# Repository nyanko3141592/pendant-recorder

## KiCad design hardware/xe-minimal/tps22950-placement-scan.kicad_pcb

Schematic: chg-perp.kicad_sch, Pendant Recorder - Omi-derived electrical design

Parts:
C1, C2, C3, C6, C9, C22, C26: 100n; C_0402_1005Metric
C4: 10u; C_0603_1608Metric
C5: 4.7u; C_0603_1608Metric
C7, C16, C25: 1u; C_0402_1005Metric
C13: 2.2u 10V; C_0402_1005Metric
C14: 2.2u; C_0402_1005Metric
C15: 10u 10V effective >=1u; C_0603_1608Metric
C27: 4.7u effective TBD; C_0603_1608Metric
C28: 10n; C_0402_1005Metric
C29: 100n 10V; C_0402_1005Metric
C30: 50p 50V C0G; C_0402_1005Metric
D6: TJ-S1005SW4TGLC9Y-A5 amber LED; LED_0402_1005Metric
J1: USB4105-GF-A (candidate); USB_C_GCT_USB4105_GroundLand112
J2: Molex781710003 / DTP401525-XE; Molex_Pico-EZmate_78171-0003_1x03-1MP_P1.20mm_Vertical
J3: Factory SWD pogo candidate; SWD_Pogo_5Pad_P1.27mm
Q3, Q4: DMN63D8L-7; SOT-23
R1: 0R; R_0402_1005Metric
R2: 10k; R_0402_1005Metric
R3, R4, R13, R15, R22: 100k; R_0402_1005Metric
R6, R7: 5.1k 1%; R_0402_1005Metric
R10: 6.8k 1%; R_0402_1005Metric
R11, R39: 20k 1%; R_0402_1005Metric
R12, R36, R37, R38, R40: 100k 1%; R_0402_1005Metric
R14: 1M; R_0402_1005Metric
R21, R23: 22R tentative; R_0402_1005Metric
R24, R25, R28: 47k; R_0402_1005Metric
R32: 6.8k tentative; R_0402_1005Metric
R33, R34: 1M 1%; R_0402_1005Metric
R35: 10k 1%; R_0402_1005Metric
R41: 7.5k 1%; R_0402_1005Metric
R42: PTFR0402B24K0P9 24k 0.1%; R_0402_1005Metric
R43: 4.7k 1%; R_0402_1005Metric
R51: 0R 1%; R_0402_1005Metric
SW1: B3U-1000P (candidate); SW_SPST_B3U-1000P
TH1: NCU18XH103F60RB 10k 1% B3380; R_0603_1608Metric
TP1, TP2, TP3, TP5, TP6: TestPoint; TestPoint_Pad_D1.0mm
U1: STM32U585CIU6; QFN-48-1EP_7x7mm_P0.5mm_EP5.6x5.6mm
U2: USBLC6-2P6; SOT-666
U3: BQ25185DLHR; Texas_DLH0010A_WSON-10-1EP_2.2x2mm_P0.4mm_EP0.9x1.5mm
U4: TPS7A0233PDBVR; SOT-23-5
U8: IM69D130V01; IM69D130_JLC_SMD_trial
U10: TPS22917DBVT; SOT-23-6
U11: CSNP32GCR01-BOW candidate; CSNP32GCR01_LGA8
U12: TLV7042DDFR; SOT-23-8

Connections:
/BAT: C14.1, J2.1 (PACK_PLUS), R33.1, TP1.1, U3.2 (BAT)
/BAT_ADC: C28.1, R33.2, R34.1, U1.11 (PA1)
/BAT_TS: J2.2 (PACK_NTC_10K), R37.2, TH1.1 (SENSE), U12.2 (INA-), U12.5 (INB+)
/BOOT0: R3.1, U1.44 (PH3)
/BUTTON_N: R4.2, SW1.1, U1.38 (PA15)
/CC1: J1.A5 (CC1), R6.1
/CC2: J1.B5 (CC2), R7.1
/CHARGER_TS: R35.1, U3.6 (TS_MR)
/CHG_ALLOW: R43.1, U1.20 (PB2)
/CHG_GUARD_GATE: Q4.1 (G), R36.1, R43.2, U12.1 (OUTA), U12.7 (OUTB)
/CHG_INHIBIT_GATE: Q4.3 (D), R12.2, U3.4 (CE_N)
/CHG_N: R11.2, U1.27 (PB14), U3.9 (STAT1)
/ILIM_VSET: R42.1, U3.7 (ILIM_VSET)
/ISET: C30.1, R10.1, U3.8 (ISET)
/NRST: C9.1, J3.3 (nRESET), R2.2, U1.7 (NRST)
/PDM_CLK: R21.2, U8.3 (CLOCK)
/PDM_CLK_MCU: R21.1, U1.39 (PB3)
/PDM_DATA: U1.40 (PB4), U8.1 (DATA)
/SD_CLK: R23.2, U11.3 (CLK)
/SD_CLK_MCU: R23.1, U1.15 (PA5)
/SD_CS_N: R28.2, U1.14 (PA4), U11.2 (CS_N)
/SD_EN: R22.1, U1.41 (PB5), U10.2 (ON)
/SD_MISO: R25.2, U1.16 (PA6), U11.6 (DO)
/SD_MOSI: R24.2, U1.17 (PA7), U11.5 (DI)
/SD_V3: C26.1, C27.1, R24.1, R25.1, R28.1, TP5.1, U10.5 (QOD), U10.6 (VOUT), U11.8 (VDD)
/STATUS_LED: R32.1, U1.29 (PA8)
/STATUS_LED_A: D6.2 (A), R32.2
/SWCLK: J3.4 (SWCLK), U1.37 (PA14)
/SWDIO: J3.2 (SWDIO), U1.34 (PA13)
/TS_COLD_REF: R38.2, R39.1, U12.3 (INA+)
/TS_HOT_REF: R40.2, R41.1, U12.6 (INB-)
/USB_DM: J1.A7 (D-), J1.B7 (D-), U1.32 (PA11), U2.3 (IO2), U2.4 (IO2)
/USB_DP: J1.A6 (D+), J1.B6 (D+), U1.33 (PA12), U2.1 (IO1), U2.6 (IO1)
/V3V3: C1.1, C2.1, C3.1, C4.1, C16.1, C22.1, C25.1, C29.1, J3.1 (VTref), R1.1, R2.1, R4.1, R11.1, R15.1, R37.1, R38.1, R40.1, TP3.1, U1.1 (VBAT), U1.24 (VDD), U1.36 (VDD), U1.48 (VDD), U4.5 (OUT), U8.2 (VDD), U10.1 (VIN), U12.8 (VCC)
/VBUS_GATE: Q3.1 (G), R13.2, R14.1
/VBUS_N: Q3.3 (D), R15.2, U1.10 (PA0)
/VCAP: C5.1, U1.22 (VCAP)
/VDDA: C6.1, C7.1, R1.2, U1.9 (VDDA)

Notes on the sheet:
01 MCU / RTC / UI
02 USB-C / CHARGER
03 POWER / FUEL GAUGE
04 AUDIO / SD / INDICATORS
ENGINEERING DRAFT - NOT FOR FABRICATION - See hardware/xe-minimal/README.md

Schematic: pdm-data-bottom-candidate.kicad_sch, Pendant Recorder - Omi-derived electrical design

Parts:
C1, C2, C3, C6, C9, C22, C26: 100n; C_0402_1005Metric
C4: 10u; C_0603_1608Metric
C5, C27: 4.7u; C_0603_1608Metric
C7, C16, C25: 1u; C_0402_1005Metric
C13: 2.2u 10V; C_0402_1005Metric
C14: 2.2u; C_0402_1005Metric
C15: 10u 10V effective >=1u; C_0603_1608Metric
C28: 10n; C_0402_1005Metric
C29: 100n 10V; C_0402_1005Metric
C30: 50p 50V C0G; C_0402_1005Metric
D6: TJ-S1005SW4TGLC9Y-A5 amber LED; LED_0402_1005Metric
J1: USB4105-GF-A; USB_C_GCT_USB4105_GroundLand112
J2: Molex781710003 / DTP401525-XE; Molex_Pico-EZmate_78171-0003_1x03-1MP_P1.20mm_Vertical
J3: Factory SWD pogo pads; SWD_Pogo_5Pad_P1.27mm
Q3, Q4: DMN63D8L-7; SOT-23
R1: 0R; R_0402_1005Metric
R2: 10k; R_0402_1005Metric
R3, R4, R13, R15, R22: 100k; R_0402_1005Metric
R6, R7: 5.1k 1%; R_0402_1005Metric
R10: RC0402FR-0730KL 30k 1%; R_0402_1005Metric
R11, R39: 20k 1%; R_0402_1005Metric
R12, R36, R37, R38, R40: 100k 1%; R_0402_1005Metric
R14: 1M; R_0402_1005Metric
R21, R23: 22R tentative; R_0402_1005Metric
R24, R25, R28: 47k; R_0402_1005Metric
R32: 6.8k tentative; R_0402_1005Metric
R33, R34: 1M 1%; R_0402_1005Metric
R35: 10k 1%; R_0402_1005Metric
R41: 7.5k 1%; R_0402_1005Metric
R42: RC0402FR-07130KL 130k 1%; R_0402_1005Metric
R43: 4.7k 1%; R_0402_1005Metric
R51: 0R 1%; R_0402_1005Metric
SW1: B3U-1000P; SW_SPST_B3U-1000P
TP1, TP2, TP3, TP5, TP6: TestPoint; TestPoint_Pad_D1.0mm
U1: STM32U585CIU6; QFN-48-1EP_7x7mm_P0.5mm_EP5.6x5.6mm
U2: USBLC6-2P6; SOT-666
U3: BQ25185DLHR; Texas_DLH0010A_WSON-10-1EP_2.2x2mm_P0.4mm_EP0.9x1.5mm
U4: TPS7A0233PDBVR; SOT-23-5
U8: IM69D130V01; IM69D130_JLC_SMD_trial
U10: TPS22917DBVT; SOT-23-6
U11: CSNP32GCR01-BOW; CSNP32GCR01_LGA8
U12: TLV7042DDFR; SOT-23-8

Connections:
/BAT: C14.1, J2.1 (PACK_PLUS), R33.1, TP1.1, U3.2 (BAT)
/BAT_ADC: C28.1, R33.2, R34.1, U1.11 (PA1)
/BAT_TS: J2.2 (PACK_NTC_10K), R37.2, U12.2 (INA-), U12.5 (INB+); also elsewhere on the board
/BOOT0: R3.1, U1.44 (PH3)
/BUTTON_N: R4.2, SW1.1, U1.38 (PA15)
/CC1: J1.A5 (CC1), R6.1
/CC2: J1.B5 (CC2), R7.1
/CHARGER_TS: R35.1, U3.6 (TS_MR)
/CHG_ALLOW: R43.1, U1.20 (PB2)
/CHG_GUARD_GATE: Q4.1 (G), R36.1, R43.2, U12.1 (OUTA), U12.7 (OUTB)
/CHG_INHIBIT_GATE: Q4.3 (D), R12.2, U3.4 (CE_N)
/CHG_N: R11.2, U1.27 (PB14), U3.9 (STAT1)
/ILIM_VSET: R42.1, U3.7 (ILIM_VSET)
/ISET: C30.1, R10.1, U3.8 (ISET)
/NRST: C9.1, J3.3 (nRESET), R2.2, U1.7 (NRST)
/PDM_CLK: R21.2, U8.3 (CLOCK)
/PDM_CLK_MCU: R21.1, U1.39 (PB3)
/PDM_DATA: U1.40 (PB4), U8.1 (DATA)
/SD_CLK: R23.2, U11.3 (CLK)
/SD_CLK_MCU: R23.1, U1.15 (PA5)
/SD_CS_N: R28.2, U1.14 (PA4), U11.2 (CS_N)
/SD_EN: R22.1, U1.41 (PB5), U10.2 (ON)
/SD_MISO: R25.2, U1.16 (PA6), U11.6 (DO)
/SD_MOSI: R24.2, U1.17 (PA7), U11.5 (DI)
/SD_V3: C26.1, C27.1, R24.1, R25.1, R28.1, TP5.1, U10.5 (QOD), U10.6 (VOUT), U11.8 (VDD)
/STATUS_LED: R32.1, U1.29 (PA8)
/STATUS_LED_A: D6.2 (A), R32.2
/SWCLK: J3.4 (SWCLK), U1.37 (PA14)
/SWDIO: J3.2 (SWDIO), U1.34 (PA13)
/TS_COLD_REF: R38.2, R39.1, U12.3 (INA+)
/TS_HOT_REF: R40.2, R41.1, U12.6 (INB-)
/USB_DM: J1.A7 (D-), J1.B7 (D-), U1.32 (PA11), U2.3 (IO2), U2.4 (IO2)
/USB_DP: J1.A6 (D+), J1.B6 (D+), U1.33 (PA12), U2.1 (IO1), U2.6 (IO1)
/V3V3: C1.1, C2.1, C3.1, C4.1, C16.1, C22.1, C25.1, C29.1, J3.1 (VTref), R1.1, R2.1, R4.1, R11.1, R15.1, R37.1, R38.1, R40.1, TP3.1, U1.1 (VBAT), U1.24 (VDD), U1.36 (VDD), U1.48 (VDD), U4.5 (OUT), U8.2 (VDD), U10.1 (VIN), U12.8 (VCC)
/VBUS_GATE: Q3.1 (G), R13.2, R14.1
/VBUS_N: Q3.3 (D), R15.2, U1.10 (PA0)
/VCAP: C5.1, U1.22 (VCAP)
/VDDA: C6.1, C7.1, R1.2, U1.9 (VDDA)

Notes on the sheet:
01 MCU / RTC / UI
02 USB-C / CHARGER
03 POWER / FUEL GAUGE
04 AUDIO / SD / INDICATORS
ENGINEERING DRAFT - NOT FOR FABRICATION - See hardware/xe-minimal/README.md

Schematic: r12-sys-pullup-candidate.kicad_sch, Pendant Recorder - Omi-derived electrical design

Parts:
C1, C2, C3, C6, C9, C22, C26: 100n; C_0402_1005Metric
C4: 10u; C_0603_1608Metric
C5, C27: 4.7u; C_0603_1608Metric
C7, C16, C25: 1u; C_0402_1005Metric
C13: 2.2u 10V; C_0402_1005Metric
C14: 2.2u; C_0402_1005Metric
C15: 10u 10V effective >=1u; C_0603_1608Metric
C28: 10n; C_0402_1005Metric
C29: 100n 10V; C_0402_1005Metric
C30: 50p 50V C0G; C_0402_1005Metric
C31, C32: 1u 10V X5R; C_0402_1005Metric
C33: 1u 35V X5R; C_0402_1005Metric
D6: TJ-S1005SW4TGLC9Y-A5 amber LED; LED_0402_1005Metric
J1: USB4105-GF-A; USB_C_GCT_USB4105_GroundLand112
J2: Molex781710003 / DTP401525-XE; Molex_Pico-EZmate_78171-0003_1x03-1MP_P1.20mm_Vertical
J3: Factory SWD pogo pads; SWD_Pogo_5Pad_P1.27mm
Q3, Q4: DMN63D8L-7; SOT-23
R1: 0R; R_0402_1005Metric
R2: 10k; R_0402_1005Metric
R3, R4, R13, R15, R22: 100k; R_0402_1005Metric
R6, R7: 5.1k 1%; R_0402_1005Metric
R10: RC0402FR-0730KL 30k 1%; R_0402_1005Metric
R11, R39: 20k 1%; R_0402_1005Metric
R12, R36, R37, R38, R40: 100k 1%; R_0402_1005Metric
R14: 1M; R_0402_1005Metric
R21, R23: 22R tentative; R_0402_1005Metric
R24, R25, R28: 47k; R_0402_1005Metric
R32: 6.8k tentative; R_0402_1005Metric
R33, R34: 1M 1%; R_0402_1005Metric
R35: 10k 1%; R_0402_1005Metric
R41: 7.5k 1%; R_0402_1005Metric
R42: RC0402FR-07130KL 130k 1%; R_0402_1005Metric
R43: 4.7k 1%; R_0402_1005Metric
SW1: B3U-1000P; SW_SPST_B3U-1000P
TP1, TP2, TP3, TP5, TP6: TestPoint; TestPoint_Pad_D1.0mm
U1: STM32U585CIU6; QFN-48-1EP_7x7mm_P0.5mm_EP5.6x5.6mm
U2: USBLC6-2P6; SOT-666
U3: BQ25185DLHR; Texas_DLH0010A_WSON-10-1EP_2.2x2mm_P0.4mm_EP0.9x1.5mm
U4: TPS7A0233PDBVR; SOT-23-5
U8: IM69D130V01; IM69D130_JLC_SMD_trial
U10: TPS22917DBVT; SOT-23-6
U11: CSNP32GCR01-BOW; CSNP32GCR01_LGA8
U12: TLV7042DDFR; SOT-23-8
U13: TPS2552DBVR-1; SOT-23-6
U14: NCP360SNT1G; SOT-23-5

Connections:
/BAT: C14.1, J2.1 (PACK_PLUS), R33.1, TP1.1, U3.2 (BAT)
/BAT_ADC: C28.1, R33.2, R34.1, U1.11 (PA1)
/BAT_TS: J2.2 (PACK_NTC_10K), R37.2, U12.2 (INA-), U12.5 (INB+); also elsewhere on the board
/BOOT0: R3.1, U1.44 (PH3)
/BUTTON_N: R4.2, SW1.1, U1.38 (PA15)
/CC1: J1.A5 (CC1), R6.1
/CC2: J1.B5 (CC2), R7.1
/CHARGER_TS: R35.1, U3.6 (TS_MR)
/CHG_ALLOW: R43.1, U1.20 (PB2)
/CHG_GUARD_GATE: Q4.1 (G), R36.1, R43.2, U12.1 (OUTA), U12.7 (OUTB)
/CHG_INHIBIT_GATE: Q4.3 (D), R12.2, U3.4 (CE_N)
/CHG_N: R11.2, U1.27 (PB14), U3.9 (STAT1)
/ILIM_VSET: R42.1, U3.7 (ILIM_VSET)
/ISET: C30.1, R10.1, U3.8 (ISET)
/NRST: C9.1, J3.3 (nRESET), R2.2, U1.7 (NRST)
/PDM_CLK: R21.2, U8.3 (CLOCK)
/PDM_CLK_MCU: R21.1, U1.39 (PB3)
/PDM_DATA: U1.40 (PB4), U8.1 (DATA)
/SD_CLK: R23.2, U11.3 (CLK)
/SD_CLK_MCU: R23.1, U1.15 (PA5)
/SD_CS_N: R28.2, U1.14 (PA4), U11.2 (CS_N)
/SD_EN: R22.1, U1.41 (PB5), U10.2 (ON)
/SD_MISO: R25.2, U1.16 (PA6), U11.6 (DO)
/SD_MOSI: R24.2, U1.17 (PA7), U11.5 (DI)
/SD_V3: C26.1, C27.1, R24.1, R25.1, R28.1, TP5.1, U10.5 (QOD), U10.6 (VOUT), U11.8 (VDD)
/STATUS_LED: R32.1, U1.29 (PA8)
/STATUS_LED_A: D6.2 (A), R32.2
/SWCLK: J3.4 (SWCLK), U1.37 (PA14)
/SWDIO: J3.2 (SWDIO), U1.34 (PA13)
/TS_COLD_REF: R38.2, R39.1, U12.3 (INA+)
/TS_HOT_REF: R40.2, R41.1, U12.6 (INB-)
/USB_DM: J1.A7 (D-), J1.B7 (D-), U1.32 (PA11), U2.3 (IO2), U2.4 (IO2)
/USB_DP: J1.A6 (D+), J1.B6 (D+), U1.33 (PA12), U2.1 (IO1), U2.6 (IO1)
/V3V3: C1.1, C2.1, C3.1, C4.1, C16.1, C22.1, C25.1, C29.1, J3.1 (VTref), R1.1, R2.1, R4.1, R11.1, R15.1, R37.1, R38.1, R40.1, TP3.1, U1.1 (VBAT), U1.24 (VDD), U1.36 (VDD), U1.48 (VDD), U4.5 (OUT), U8.2 (VDD), U10.1 (VIN), U12.8 (VCC)
/VBUS_GATE: Q3.1 (G), R13.2, R14.1
/VBUS_N: Q3.3 (D), R15.2, U1.10 (PA0)
/VCAP: C5.1, U1.22 (VCAP)
/VDDA: C6.1, C7.1, R1.2, U1.9 (VDDA)

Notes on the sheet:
01 MCU / RTC / UI
02 USB-C / CHARGER
03 POWER / FUEL GAUGE
04 AUDIO / SD / INDICATORS
ENGINEERING DRAFT - NOT FOR FABRICATION - See hardware/xe-minimal/README.md

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
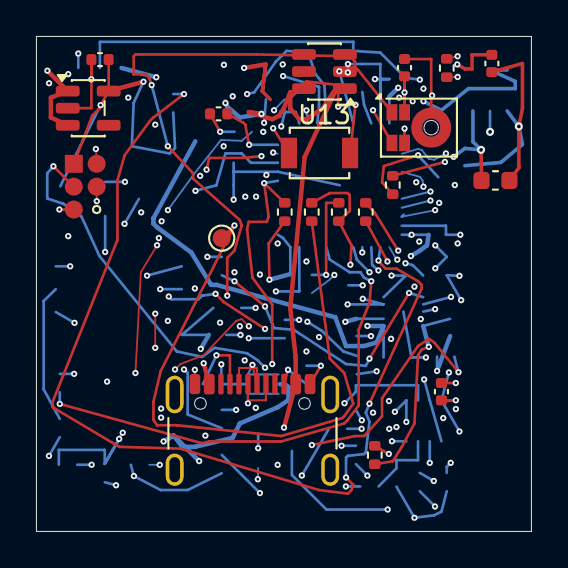
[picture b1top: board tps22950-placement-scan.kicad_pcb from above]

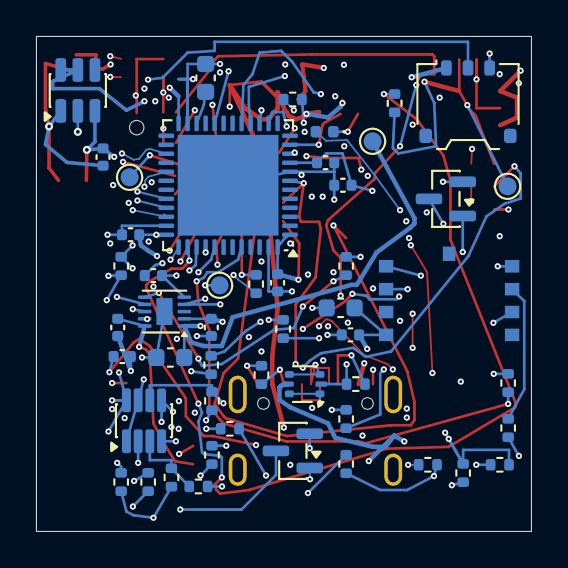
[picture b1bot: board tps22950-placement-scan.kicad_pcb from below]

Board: 6 copper layers, 27.5 x 27.5 mm, 70 parts (50 on the bottom side), 42 nets.

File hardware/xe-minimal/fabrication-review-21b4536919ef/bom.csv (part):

Reference,Part/value,Footprint,Design note
U1,STM32U585CIU6,Package_DFN_QFN:QFN-48-1EP_7x7mm_P0.5mm_EP5.6x5.6mm,2MB Flash/786KB RAM; non-SMPS UFQFPN48. PB3/PB4 ADF AF3; PA5/6/7 SPI1 AF5. VDD USB shared 3.3V. JLC C5271026 Economic/Standard catalog match; ordinary stock and physical EVT pending.
C1,100n,Capacitor_SMD:C_0402_1005Metric,
C4,10u,Capacitor_SMD:C_0603_1608Metric,Main bulk capacitor; check startup and effective capacitance.
C9,100n,Capacitor_SMD:C_0402_1005Metric,
R2,10k,Resistor_SMD:R_0402_1005Metric,
J3,Factory SWD pogo pads,PendantMinimal:SWD_Pogo_5Pad_P1.27mm,Five exposed PCB pads; factory fixture required; VTref sense only. No assembly part and no buyer flashing.
SW1,B3U-1000P,Button_Switch_SMD:SW_SPST_B3U-1000P,JLC C231329 Economic/Standard catalog match; actuation and case-button EVT pending.
R4,100k,Resistor_SMD:R_0402_1005Metric,
J1,USB4105-GF-A,PendantD1:USB_C_GCT_USB4105_GroundLand112,JLC C3020560 Economic/Standard catalog match. Exact GCT land pattern and shield numbering audited; cable fit and high-difficulty assembly yield require EVT.
R6,5.1k 1%,Resistor_SMD:R_0402_1005Metric,
R7,5.1k 1%,Resistor_SMD:R_0402_1005Metric,
U2,USBLC6-2P6,Package_TO_SOT_SMD:SOT-666,"ST DS4260 SOT-666 pinout; JLC C15999 Economic/Standard catalog match. Orientation and land pattern are synchronized; USB ESD physical qualification pending."
C13,2.2u 10V,Capacitor_SMD:C_0402_1005Metric,
U3,BQ25185DLHR,Package_DFN_QFN:Texas_DLH0010A_WSON-10-1EP_2.2x2mm_P0.4mm_EP0.9x1.5mm,"BQ25185 Rev.B: R42=130k selects 4.1V nominal (4.1205V guaranteed maximum) and internal ILIM500; R10=30k gives 9..11mA fast charge. Upstream U13 TPS22950 with R51=20k bounds guaranteed total USB input to 66.06mA. Physical charge, transient, thermal and recovery qualification pending."
R10,RC0402FR-0730KL 30k 1%,Resistor_SMD:R_0402_1005Metric,"BQ25185 characterized 9..11mA fast charge at 30k; nominal termination 1.0mA and characterized upper 1.1mA. JLC C138008 stock 600357 observed 2026-10-28."
R11,20k 1%,Resistor_SMD:R_0402_1005Metric,
C14,2.2u,Capacitor_SMD:C_0402_1005Metric,
J2,Molex781710003 / DTP401525-XE,Connector_Molex:Molex_Pico-EZmate_78171-0003_1x03-1MP_P1.20mm_Vertical,"DTP401525-XE fixed pack: P1 red BAT+, P2 white built-in 10k NTC, P3 black GND. Pack NTC drives the independent hardware hot/cold charge-inhibit comparators directly. Exact R-T curve remains a receiving-inspection and EVT requirement; no user wiring."
R12,100k 1%,Resistor_SMD:R_0402_1005Metric,"YAGEO RC0402FR-07100KL; 100k 1%, +/-100ppm/C. Pulls U3 CE high from VBUS_LIMITED to inhibit charging when Q4 is off; no Q2 in this path."
C15,10u 10V effective >=1u,Capacitor_SMD:C_0603_1608Metric,SYS cap per TI; DC-bias capacitance must be qualified.
U4,TPS7A0233PDBVR,Package_TO_SOT_SMD:SOT-23-5,3.3V main rail: 48-pin MCU has no separate USB supply; dropout/capacity measurement required.
C16,1u,Capacitor_SMD:C_0402_1005Metric,
C31,1u 10V X5R,Capacitor_SMD:C_0402_1005Metric,TPS22950 VIN local bypass; placed adjacent to U13 per TI SLVSFJ2B section 10.3/10.4; effective capacitance and transient behavior require EVT.
C32,1u 10V X5R,Capacitor_SMD:C_0402_1005Metric,TPS22950 VOUT local bypass; placed directly below U13 with short filled-via connection; effective capacitance and transient behavior require EVT.
U8,IM69D130V01,Pendant:IM69D130_JLC_SMD_trial,"Direct 3.3V PDM, bottom port; no AAD. 0.768MHz/decimation48 candidate for 16kHz; acoustic validation required."
R21,22R tentative,Resistor_SMD:R_0402_1005Metric,
C22,100n,Capacitor_SMD:C_0402_1005Metric,
U10,TPS22917DBVT,Package_TO_SOT_SMD:SOT-23-6,"TPS22917DBVT load switch. CT is intentionally open for the TI-specified fastest turn-on; QOD is tied to SD_V3. Rise time, discharge and reverse-current behavior require EVT."
R22,100k,Resistor_SMD:R_0402_1005Metric,
C25,1u,Capacitor_SMD:C_0402_1005Metric,
R23,22R tentative,Resistor_SMD:R_0402_1005Metric,
R24,47k,Resistor_SMD:R_0402_1005Metric,
R25,47k,Resistor_SMD:R_0402_1005Metric,
R28,47k,Resistor_SMD:R_0402_1005Metric,
C26,100n,Capacitor_SMD:C_0402_1005Metric,
C27,4.7u,Capacitor_SMD:C_0603_1608Metric,HGC0603R7475K160NTHJ / C49333233 16 V X7R ±10% selected with C5; replaces non-orderable C6119855; voltage-bias and storage-inrush EVT pending.
TP1,TestPoint,TestPoint:TestPoint_Pad_D1.0mm,
TP2,TestPoint,TestPoint:TestPoint_Pad_D1.0mm,
TP3,TestPoint,TestPoint:TestPoint_Pad_D1.0mm,
TP5,TestPoint,TestPoint:TestPoint_Pad_D1.0mm,
TP6,TestPoint,TestPoint:TestPoint_Pad_D1.0mm,
R32,6.8k tentative,Resistor_SMD:R_0402_1005Metric,"LED current target 0.1-0.2mA; verify LED Vf, daylight readability and GPIO limits"
D6,TJ-S1005SW4TGLC9Y-A5 amber LED,LED_SMD:LED_0402_1005Metric,"Single status/battery indicator; JLC C273600 observed stock 6011 on 2026-10-28; firmware blinks on demand, normally dark."
C2,100n,Capacitor_SMD:C_0402_1005Metric,
C3,100n,Capacitor_SMD:C_0402_1005Metric,
C5,4.7u,Capacitor_SMD:C_0603_1608Metric,HGC0603R7475K160NTHJ / C49333233 16 V X7R ±10%; replaces non-orderable C6119855; VCAP effective-capacitance EVT pending.
C6,100n,Capacitor_SMD:C_0402_1005Metric,
C7,1u,Capacitor_SMD:C_0402_1005Metric,
R1,0R,Resistor_SMD:R_0402_1005Metric,
R3,100k,Resistor_SMD:R_0402_1005Metric,
Q3,DMN63D8L-7,Package_TO_SOT_SMD:SOT-23,"Diodes DMN63D8L-7 selected for engineering prototype VBUS presence detection; pin1 G pin2 S pin3 D. Temperature, detection and solder process qualification pending."
R13,100k,Resistor_SMD:R_0402_1005Metric,Purchase specification: YAGEO RC0402FR-07100KL; 0402; 1%; +/-100 ppm/C; 0.063 W at 70 C; 50 V working limit. Supplier SKU/price and circuit qualification pending.
R14,1M,Resistor_SMD:R_0402_1005Metric,Purchase specification: YAGEO RC0402FR-071ML; 0402; 1%; +/-100 ppm/C; 0.063 W at 70 C; 50 V working limit. Supplier SKU/price and circuit qualification pending.
R15,100k,Resistor_SMD:R_0402_1005Metric,Purchase specification: YAGEO RC0402FR-07100KL; 0402; 1%; +/-100 ppm/C; 0.063 W at 70 C; 50 V working limit. Supplier SKU/price and circuit qualification pending.
R33,1M 1%,Resistor_SMD:R_0402_1005Metric,"Battery divider 1:2; sample after settling, calibrate with VREFINT; not coulomb counting."
R34,1M 1%,Resistor_SMD:R_0402_1005Metric,"Battery divider 1:2; sample after settling, calibrate with VREFINT; not coulomb counting."
C28,10n,Capacitor_SMD:C_0402_1005Metric,"Battery divider 1:2; sample after settling, calibrate with VREFINT; not coulomb counting."
R35,10k 1%,Resistor_SMD:R_0402_1005Metric,Holds normal TS level when released; no floating TS/TTDM in intended circuit.
R36,100k 1%,Resistor_SMD:R_0402_1005Metric,"YAGEO RC0402FR-07100KL; 100k 1%, +/-100ppm/C. Reset/high-Z gate pulldown; no charging permission."
R37,100k 1%,Resistor_SMD:R_0402_1005Metric,Reduce thermistor excitation; 5.25V and99k gives52.99uA maximum branch current and69.60uW maximum thermistor power. Only powered from USB. Shared MCU rail for USB-independent temperature guard; BOR4 and startup timing qualification required.
R38,100k 1%,Resistor_SMD:R_0402_1005Metric, Shared MCU rail for USB-independent temperature guard; BOR4 and startup timing qualification required.
R39,20k 1%,Resistor_SMD:R_0402_1005Metric,Cold threshold candidate. Beta-model sensitivity is not full manufacturer R-T qualification. See temperature-screen.json.
R40,100k 1%,Resistor_SMD:R_0402_1005Metric, Shared MCU rail for USB-independent temperature guard; BOR4 and startup timing qualification required.
R41,7.5k 1%,Resistor_SMD:R_0402_1005Metric,Hot threshold candidate. Reserve margin for contact sensor lag; physical thermal qualification required.
U12,TLV7042DDFR,Package_TO_SOT_SMD:SOT-23-8,"TLV7042 open-drain wired-AND temperature permission. Either fault pulls Q4 gate low. BAT_TS is driven by the fixed pack's internal 10k NTC; comparator tolerance, pack R-T lot spread, startup and installed thermal lag require EVT."
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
